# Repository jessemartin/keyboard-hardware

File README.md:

Wireless Keyboard Project: Hardware
===================================

These are [Eagle](https://www.autodesk.com/products/eagle/overview) design files for PCBs used in my wireless keyboard project.

Engineering Overview
--------------------
Each keyboard section runs a [Nordic nRF51822](https://www.nordicsemi.com/eng/Products/Bluetooth-low-energy/nRF51822) in the [Waveshare core51822-b](https://www.waveshare.com/core51822-b.htm) package, powered by a lithium ion battery.

Instead of using a traditional matrix that requires constant scanning (and thereby constant power usage), each key is connected to its own dedicated pin. This way, the chip can enter sleep until interrupted by a key press.

When a key press occurs, it is first debounced to prevent the mechanical switch from generating extra key presses. After that, the pressed keys are collected and transmitted through the [Gazell protocol](https://infocenter.nordicsemi.com/index.jsp?topic=%2Fcom.nordic.infocenter.sdk5.v11.0.0%2Flib_gzp.html&cp=4_0_7_3_10) to the receiver.

The receiver transforms the pressed keys into a matrix and passes that off the the [ATmega32U4 Pro Micro](https://www.sparkfun.com/products/12640), which runs [QMK firmware](https://github.com/qmk/qmk_firmware/). The Pro Micro sends the signal over USB to the computer as input.

Keyboard Layout
---------------
http://www.keyboard-layout-editor.com/#/gists/4d522280e8e3315902466de2c982f663

Folder Structure
----------------
 - `3d` contains [SketchUp](https://app.sketchup.com/app) renderings of what the final product could look like. These are not dimensionally accurate.
 - `fab` contains design rules and CAM settings for [DirtyPCBs](https://dirtypcbs.com/store/pcbs) and [OSH Park](https://oshpark.com/)
 - `lib` contains device libraries that are used by the `receiver` and `keyboard` projects.

PCB Fab Specifications
----------------------
* FR4 fiberglass
* 2 layer
* 1.6mm thickness

Keyboard PCBs
-------------

A single, reversible board is used for each keyboard half. The top of the board is used for the left half, and the bottom for the right half:

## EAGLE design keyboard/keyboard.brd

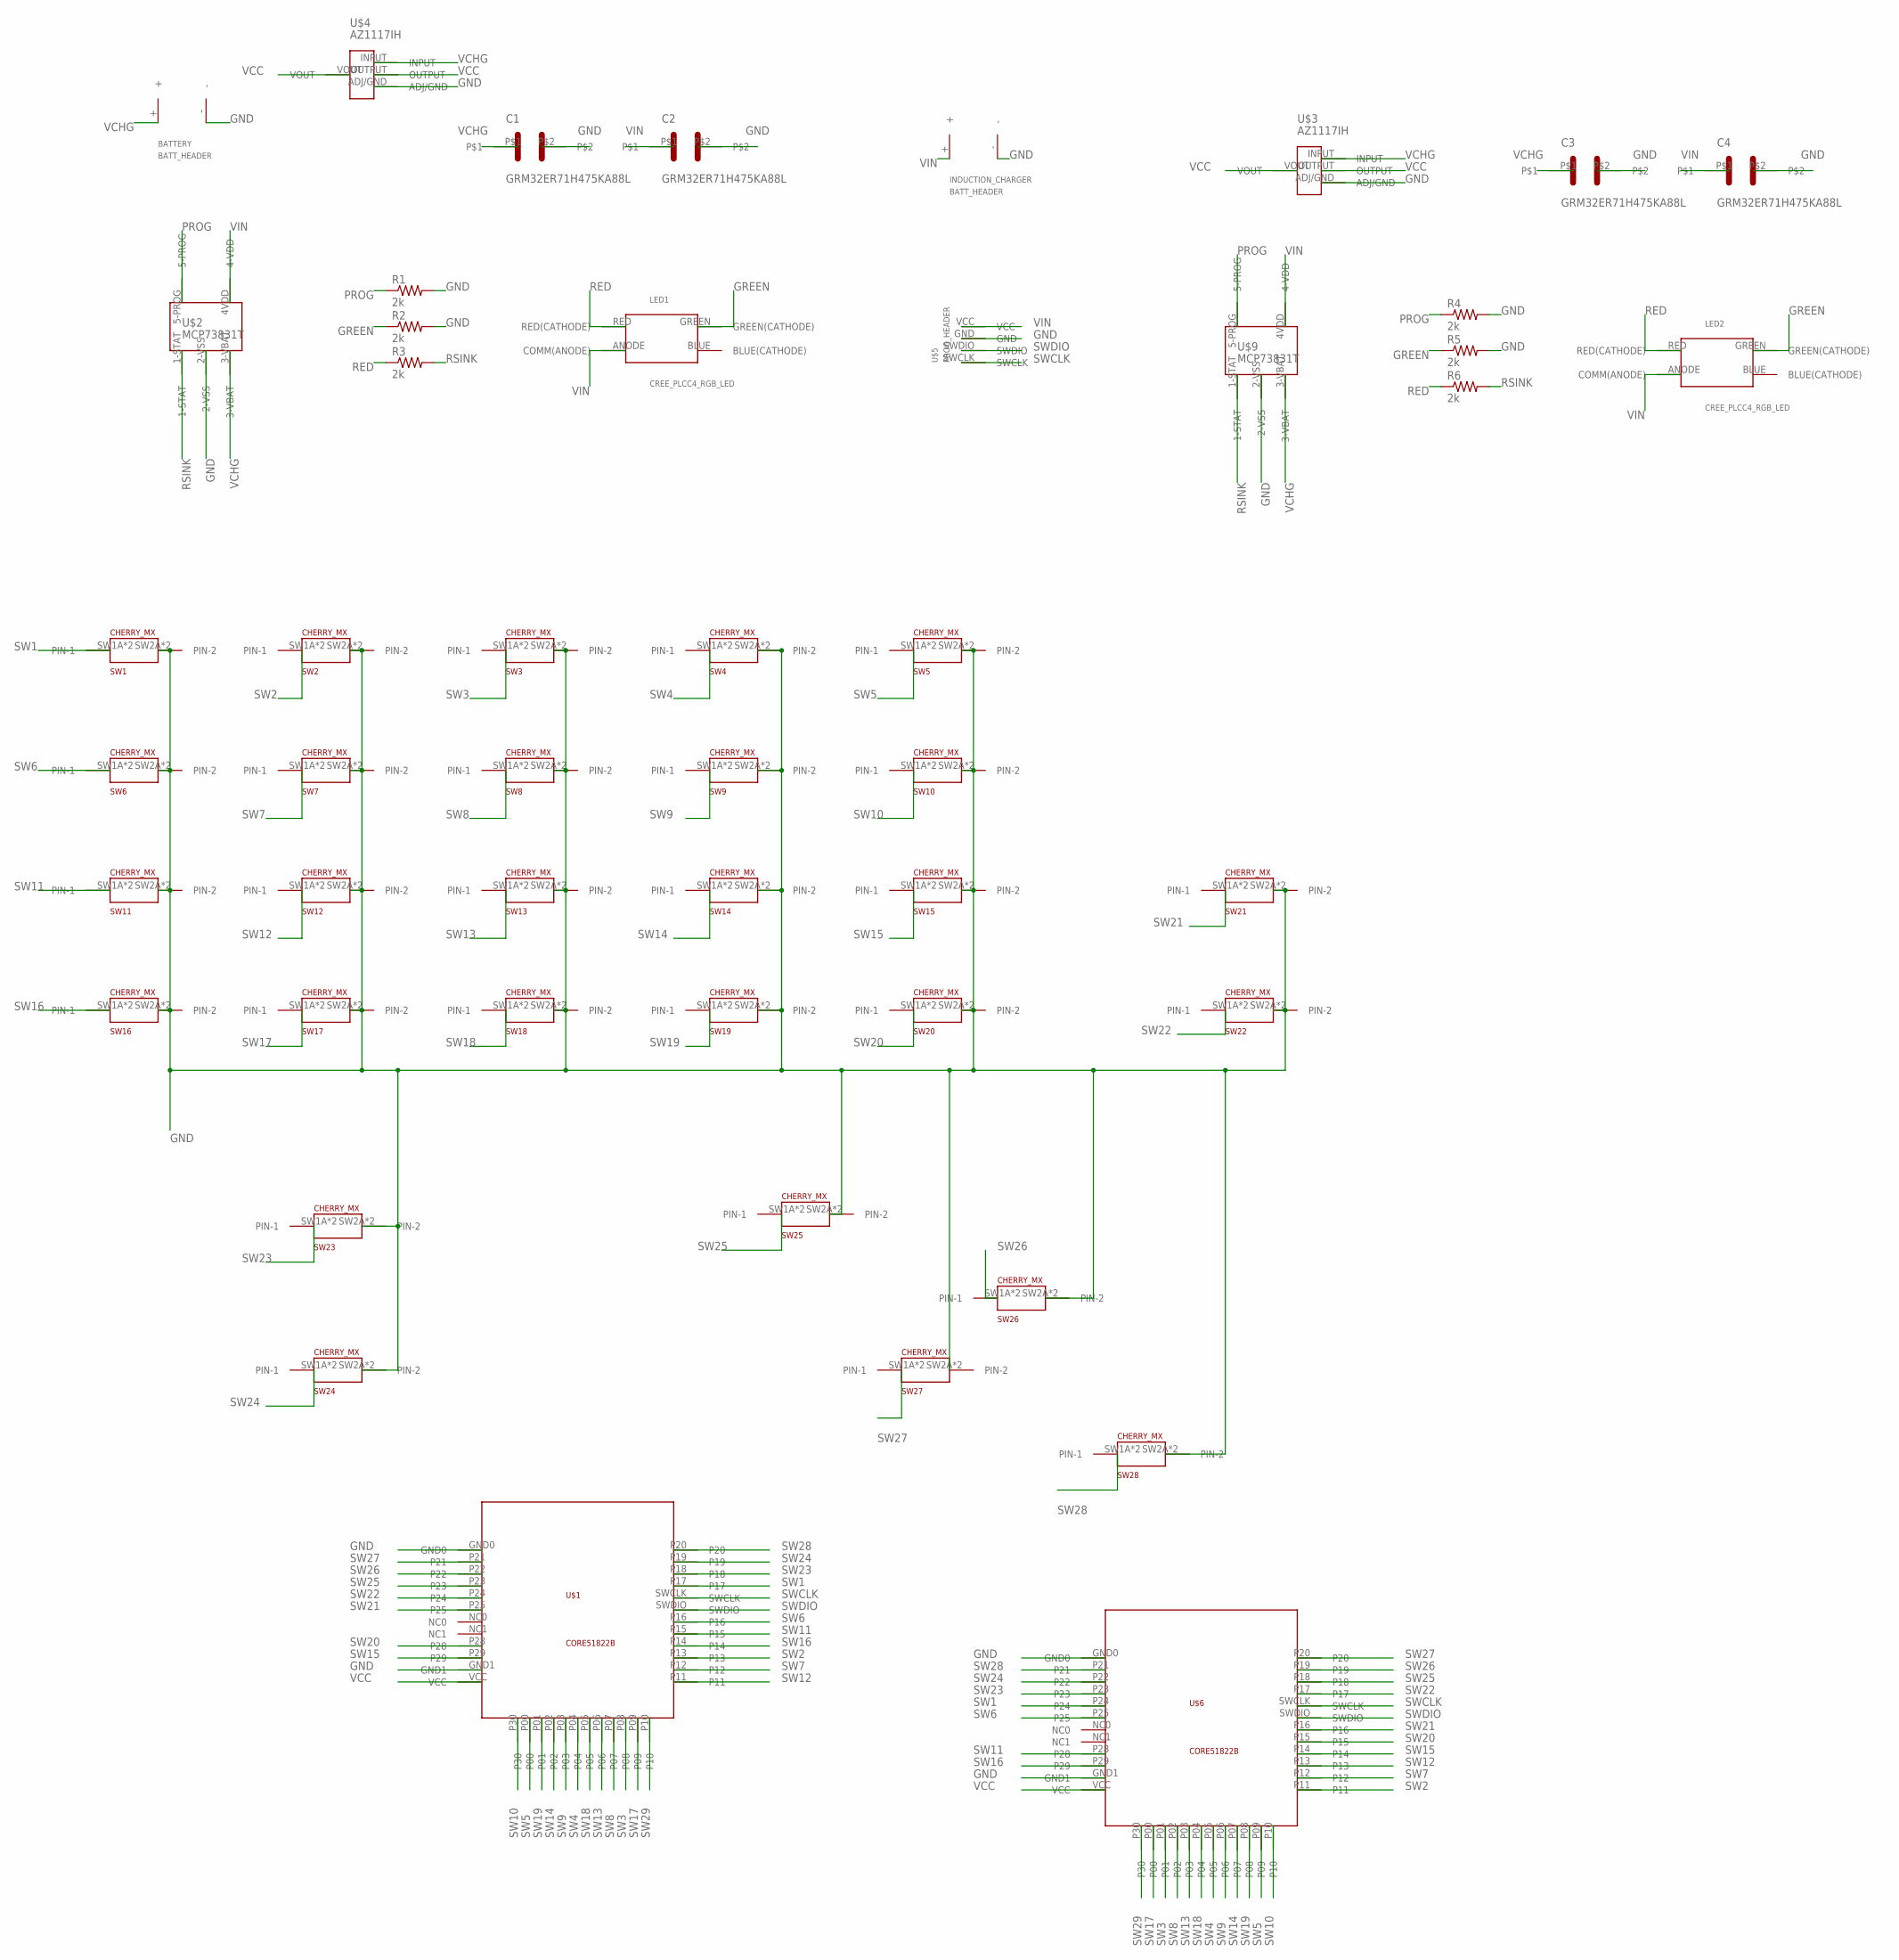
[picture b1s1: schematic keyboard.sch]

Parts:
BATTERY: BATT_HEADER
C1, C2, C3, C4: GRM32ER71H475KA88L
INDUCTION_CHARGER: BATT_HEADER
LED1, LED2: CREE_PLCC4_RGB_LED; 4-PLCC
R1, R2, R3, R4, R5, R6: 2k; R1210
SW1, SW2, SW3, SW4, SW5, SW6, SW7, SW8, SW9, SW10, SW11, SW12, SW13, SW14, SW15, SW16, SW17, SW18, SW19, SW20, SW21, SW22, SW23, SW24, SW25, SW26, SW27, SW28: CHERRY_MX
U$1, U$6: CORE51822B
U$2, U$9: MCP73831T
U$3, U$4: AZ1117IH
U$5: PROG_HEADER

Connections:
GND: BATTERY.-, C1.P$2, C2.P$2, C3.P$2, C4.P$2, INDUCTION_CHARGER.-, R1.2, R2.2, R4.2, R5.2, SW1.SW2A (PIN-2), SW1.SW2B (PIN-2), SW2.SW2A (PIN-2), SW2.SW2B (PIN-2), SW3.SW2A (PIN-2), SW3.SW2B (PIN-2), SW4.SW2A (PIN-2), SW4.SW2B (PIN-2), SW5.SW2A (PIN-2), SW5.SW2B (PIN-2), SW6.SW2A (PIN-2), SW6.SW2B (PIN-2), SW7.SW2A (PIN-2), SW7.SW2B (PIN-2), SW8.SW2A (PIN-2), SW8.SW2B (PIN-2), SW9.SW2A (PIN-2), SW9.SW2B (PIN-2), SW10.SW2A (PIN-2), SW10.SW2B (PIN-2), SW11.SW2A (PIN-2), SW11.SW2B (PIN-2), SW12.SW2A (PIN-2), SW12.SW2B (PIN-2), SW13.SW2A (PIN-2), SW13.SW2B (PIN-2), SW14.SW2A (PIN-2), SW14.SW2B (PIN-2), SW15.SW2A (PIN-2), SW15.SW2B (PIN-2), SW16.SW2A (PIN-2), SW16.SW2B (PIN-2), SW17.SW2A (PIN-2), SW17.SW2B (PIN-2), SW18.SW2A (PIN-2), SW18.SW2B (PIN-2), SW19.SW2A (PIN-2), SW19.SW2B (PIN-2), SW20.SW2A (PIN-2), SW20.SW2B (PIN-2), SW21.SW2A (PIN-2), SW21.SW2B (PIN-2), SW22.SW2A (PIN-2), SW22.SW2B (PIN-2), SW23.SW2A (PIN-2), SW23.SW2B (PIN-2), SW24.SW2A (PIN-2), SW24.SW2B (PIN-2), SW25.SW2A (PIN-2), SW25.SW2B (PIN-2), SW26.SW2A (PIN-2), SW26.SW2B (PIN-2), SW27.SW2A (PIN-2), SW27.SW2B (PIN-2), SW28.SW2A (PIN-2), SW28.SW2B (PIN-2), U$1.GND0, U$1.GND1, U$2.2-VSS, U$3.ADJ/GND, U$4.ADJ/GND, U$5.GND, U$6.GND0, U$6.GND1, U$9.2-VSS
GREEN: LED1.GREEN (GREEN(CATHODE)), LED2.GREEN (GREEN(CATHODE)), R2.1, R5.1
PROG: R1.1, R4.1, U$2.5-PROG, U$9.5-PROG
RED: LED1.RED (RED(CATHODE)), LED2.RED (RED(CATHODE)), R3.1, R6.1
RSINK: R3.2, R6.2, U$2.1-STAT, U$9.1-STAT
SW1: SW1.SW1A (PIN-1), SW1.SW1B (PIN-1), U$1.P17, U$6.P24
SW2: SW2.SW1A (PIN-1), SW2.SW1B (PIN-1), U$1.P13, U$6.P11
SW3: SW3.SW1A (PIN-1), SW3.SW1B (PIN-1), U$1.P08, U$6.P01
SW4: SW4.SW1A (PIN-1), SW4.SW1B (PIN-1), U$1.P04, U$6.P05
SW5: SW5.SW1A (PIN-1), SW5.SW1B (PIN-1), U$1.P00, U$6.P09
SW6: SW6.SW1A (PIN-1), SW6.SW1B (PIN-1), U$1.P16, U$6.P25
SW7: SW7.SW1A (PIN-1), SW7.SW1B (PIN-1), U$1.P12, U$6.P12
SW8: SW8.SW1A (PIN-1), SW8.SW1B (PIN-1), U$1.P07, U$6.P02
SW9: SW9.SW1A (PIN-1), SW9.SW1B (PIN-1), U$1.P03, U$6.P06
SW10: SW10.SW1A (PIN-1), SW10.SW1B (PIN-1), U$1.P30, U$6.P10
SW11: SW11.SW1A (PIN-1), SW11.SW1B (PIN-1), U$1.P15, U$6.P28
SW12: SW12.SW1A (PIN-1), SW12.SW1B (PIN-1), U$1.P11, U$6.P13
SW13: SW13.SW1A (PIN-1), SW13.SW1B (PIN-1), U$1.P06, U$6.P03
SW14: SW14.SW1A (PIN-1), SW14.SW1B (PIN-1), U$1.P02, U$6.P07
SW15: SW15.SW1A (PIN-1), SW15.SW1B (PIN-1), U$1.P29, U$6.P14
SW16: SW16.SW1A (PIN-1), SW16.SW1B (PIN-1), U$1.P14, U$6.P29
SW17: SW17.SW1A (PIN-1), SW17.SW1B (PIN-1), U$1.P09, U$6.P00
SW18: SW18.SW1A (PIN-1), SW18.SW1B (PIN-1), U$1.P05, U$6.P04
SW19: SW19.SW1A (PIN-1), SW19.SW1B (PIN-1), U$1.P01, U$6.P08
SW20: SW20.SW1A (PIN-1), SW20.SW1B (PIN-1), U$1.P28, U$6.P15
SW21: SW21.SW1A (PIN-1), SW21.SW1B (PIN-1), U$1.P25, U$6.P16
SW22: SW22.SW1A (PIN-1), SW22.SW1B (PIN-1), U$1.P24, U$6.P17
SW23: SW23.SW1A (PIN-1), SW23.SW1B (PIN-1), U$1.P18, U$6.P23
SW24: SW24.SW1A (PIN-1), SW24.SW1B (PIN-1), U$1.P19, U$6.P22
SW25: SW25.SW1A (PIN-1), SW25.SW1B (PIN-1), U$1.P23, U$6.P18
SW26: SW26.SW1A (PIN-1), SW26.SW1B (PIN-1), U$1.P22, U$6.P19
SW27: SW27.SW1A (PIN-1), SW27.SW1B (PIN-1), U$1.P21, U$6.P20
SW28: SW28.SW1A (PIN-1), SW28.SW1B (PIN-1), U$1.P20, U$6.P21
SW29: U$1.P10, U$6.P30
SWCLK: U$1.SWCLK, U$5.SWCLK, U$6.SWCLK
SWDIO: U$1.SWDIO, U$5.SWDIO, U$6.SWDIO
VCC: U$1.VCC, U$3.OUTPUT, U$3.VOUT, U$4.OUTPUT, U$4.VOUT, U$6.VCC
VCHG: BATTERY.+, C1.P$1, C3.P$1, U$2.3-VBAT, U$3.INPUT, U$4.INPUT, U$9.3-VBAT
VIN: C2.P$1, C4.P$1, INDUCTION_CHARGER.+, LED1.ANODE (COMM(ANODE)), LED2.ANODE (COMM(ANODE)), U$2.4VDD (4-VDD), U$5.VCC, U$9.4VDD (4-VDD)

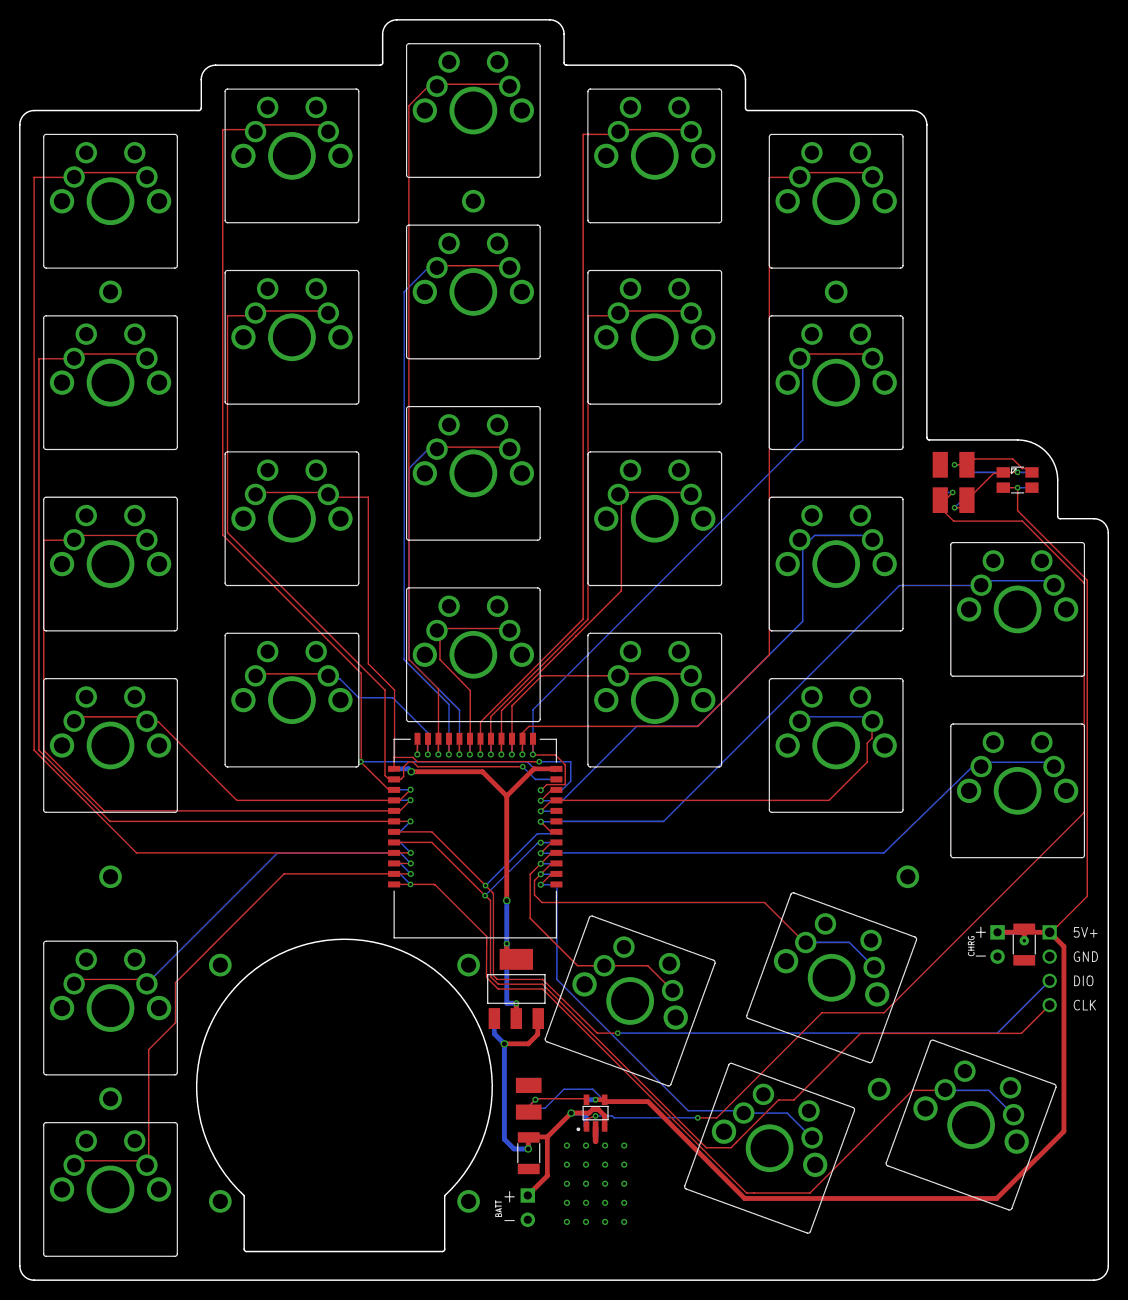
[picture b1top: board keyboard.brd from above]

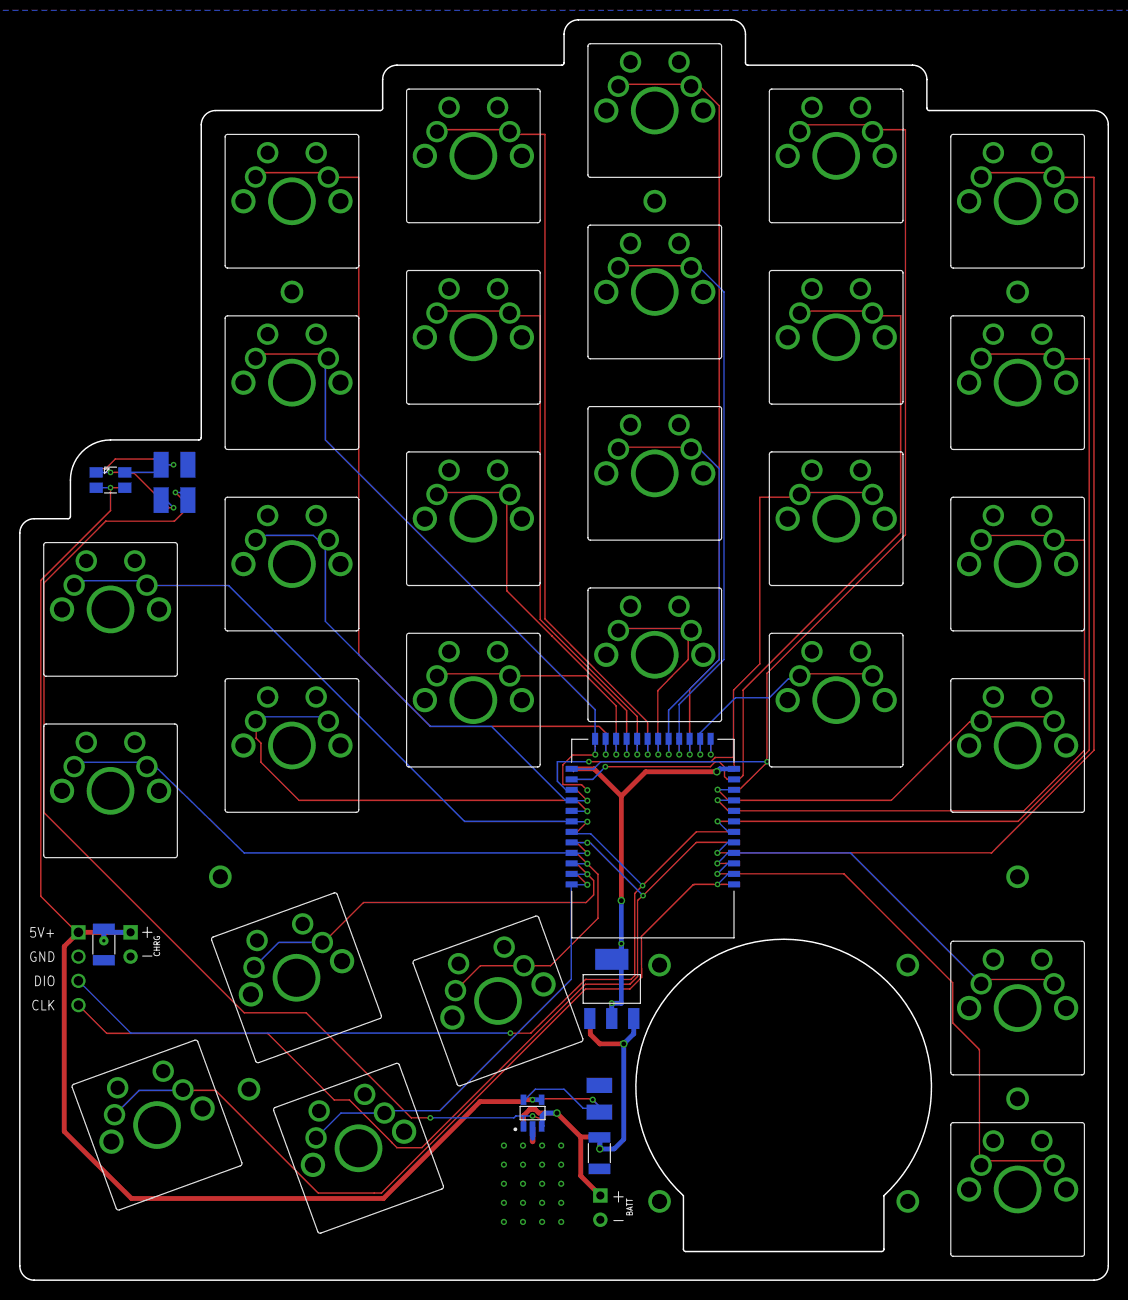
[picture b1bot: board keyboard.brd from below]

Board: 2 copper layers, 114.0 x 132.0 mm, 49 parts (9 on the bottom side), 39 nets.

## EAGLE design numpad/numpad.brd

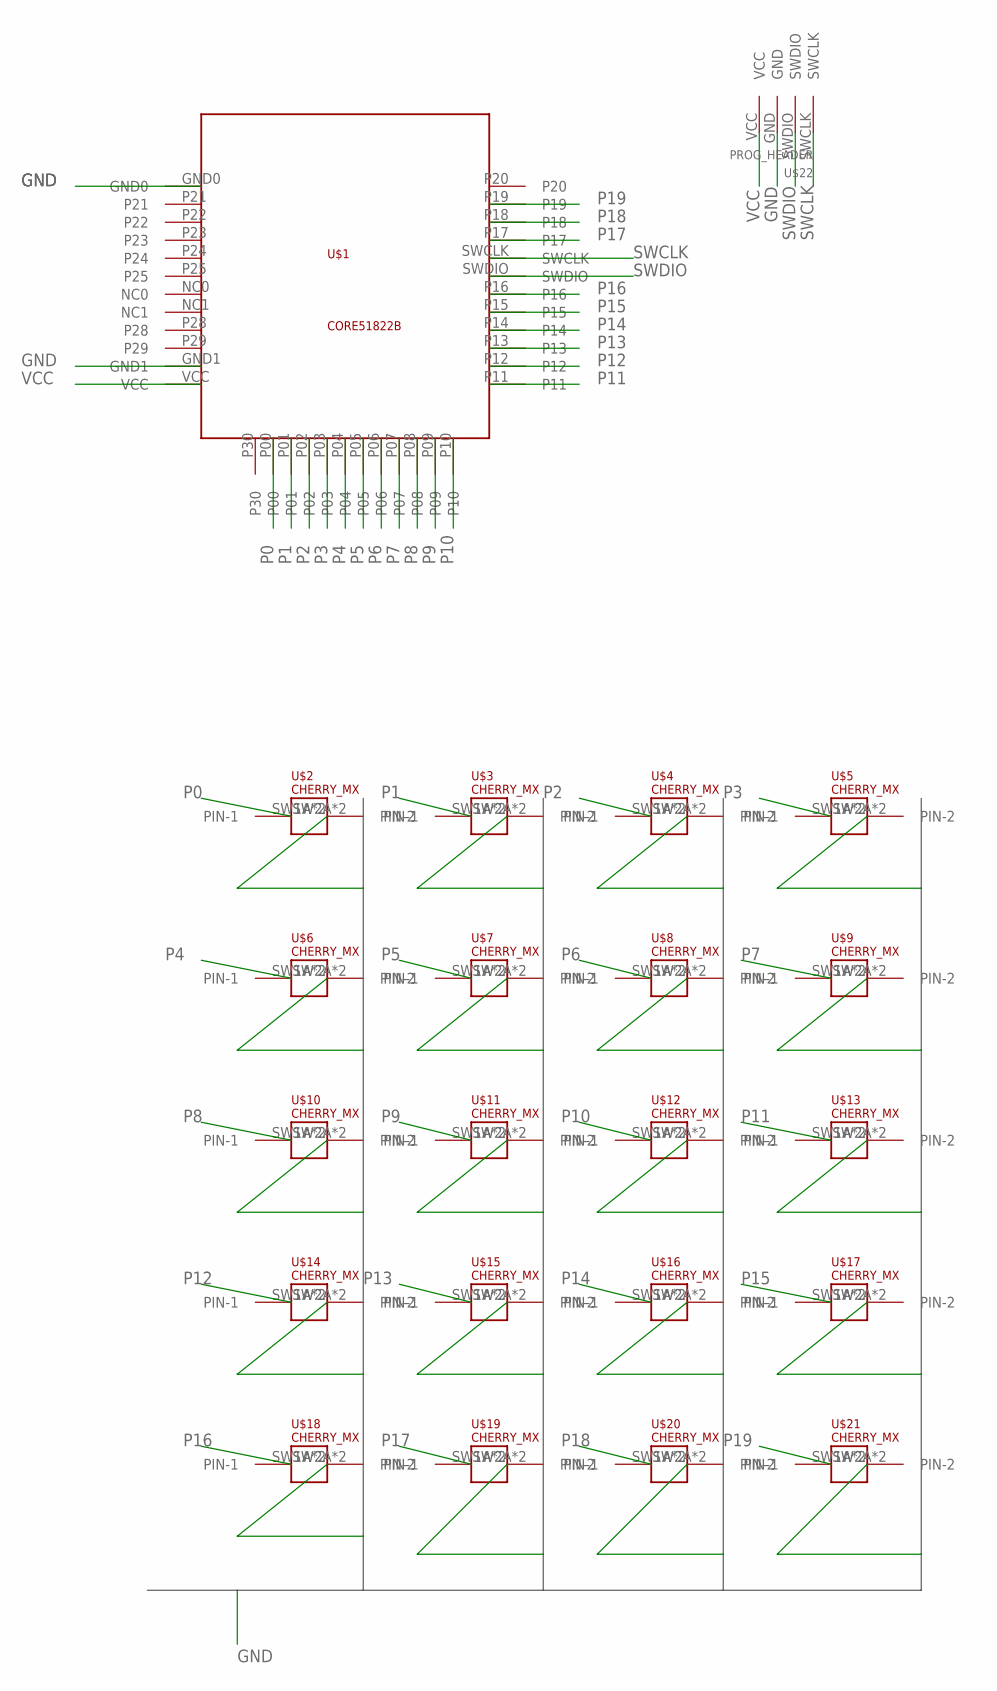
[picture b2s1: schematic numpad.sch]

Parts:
U$1: CORE51822B
U$2, U$3, U$4, U$5, U$6, U$7, U$8, U$9, U$10, U$11, U$12, U$13, U$14, U$15, U$16, U$17, U$18, U$19, U$20, U$21: CHERRY_MX
U$22: PROG_HEADER

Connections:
B$1: U$2.SW2A (PIN-2), U$2.SW2B (PIN-2), U$3.SW2A (PIN-2), U$3.SW2B (PIN-2), U$4.SW2A (PIN-2), U$4.SW2B (PIN-2), U$5.SW2A (PIN-2), U$5.SW2B (PIN-2), U$6.SW2A (PIN-2), U$6.SW2B (PIN-2), U$7.SW2A (PIN-2), U$7.SW2B (PIN-2), U$8.SW2A (PIN-2), U$8.SW2B (PIN-2), U$9.SW2A (PIN-2), U$9.SW2B (PIN-2), U$10.SW2A (PIN-2), U$10.SW2B (PIN-2), U$11.SW2A (PIN-2), U$11.SW2B (PIN-2), U$12.SW2A (PIN-2), U$12.SW2B (PIN-2), U$13.SW2A (PIN-2), U$13.SW2B (PIN-2), U$14.SW2A (PIN-2), U$14.SW2B (PIN-2), U$15.SW2A (PIN-2), U$15.SW2B (PIN-2), U$16.SW2A (PIN-2), U$16.SW2B (PIN-2), U$17.SW2A (PIN-2), U$17.SW2B (PIN-2), U$18.SW2A (PIN-2), U$18.SW2B (PIN-2), U$19.SW2A (PIN-2), U$19.SW2B (PIN-2), U$20.SW2A (PIN-2), U$20.SW2B (PIN-2), U$21.SW2A (PIN-2), U$21.SW2B (PIN-2)
GND: U$1.GND0, U$1.GND1, U$22.GND
P0: U$1.P00, U$2.SW1A (PIN-1), U$2.SW1B (PIN-1)
P1: U$1.P01, U$3.SW1A (PIN-1), U$3.SW1B (PIN-1)
P2: U$1.P02, U$4.SW1A (PIN-1), U$4.SW1B (PIN-1)
P3: U$1.P03, U$5.SW1A (PIN-1), U$5.SW1B (PIN-1)
P4: U$1.P04, U$6.SW1A (PIN-1), U$6.SW1B (PIN-1)
P5: U$1.P05, U$7.SW1A (PIN-1), U$7.SW1B (PIN-1)
P6: U$1.P06, U$8.SW1A (PIN-1), U$8.SW1B (PIN-1)
P7: U$1.P07, U$9.SW1A (PIN-1), U$9.SW1B (PIN-1)
P8: U$1.P08, U$10.SW1A (PIN-1), U$10.SW1B (PIN-1)
P9: U$1.P09, U$11.SW1A (PIN-1), U$11.SW1B (PIN-1)
P10: U$1.P10, U$12.SW1A (PIN-1), U$12.SW1B (PIN-1)
P11: U$1.P11, U$13.SW1A (PIN-1), U$13.SW1B (PIN-1)
P12: U$1.P12, U$14.SW1A (PIN-1), U$14.SW1B (PIN-1)
P13: U$1.P13, U$15.SW1A (PIN-1), U$15.SW1B (PIN-1)
P14: U$1.P14, U$16.SW1A (PIN-1), U$16.SW1B (PIN-1)
P15: U$1.P15, U$17.SW1A (PIN-1), U$17.SW1B (PIN-1)
P16: U$1.P16, U$18.SW1A (PIN-1), U$18.SW1B (PIN-1)
P17: U$1.P17, U$19.SW1A (PIN-1), U$19.SW1B (PIN-1)
P18: U$1.P18, U$20.SW1A (PIN-1), U$20.SW1B (PIN-1)
P19: U$1.P19, U$21.SW1A (PIN-1), U$21.SW1B (PIN-1)
SWCLK: U$1.SWCLK, U$22.SWCLK
SWDIO: U$1.SWDIO, U$22.SWDIO
VCC: U$1.VCC, U$22.VCC

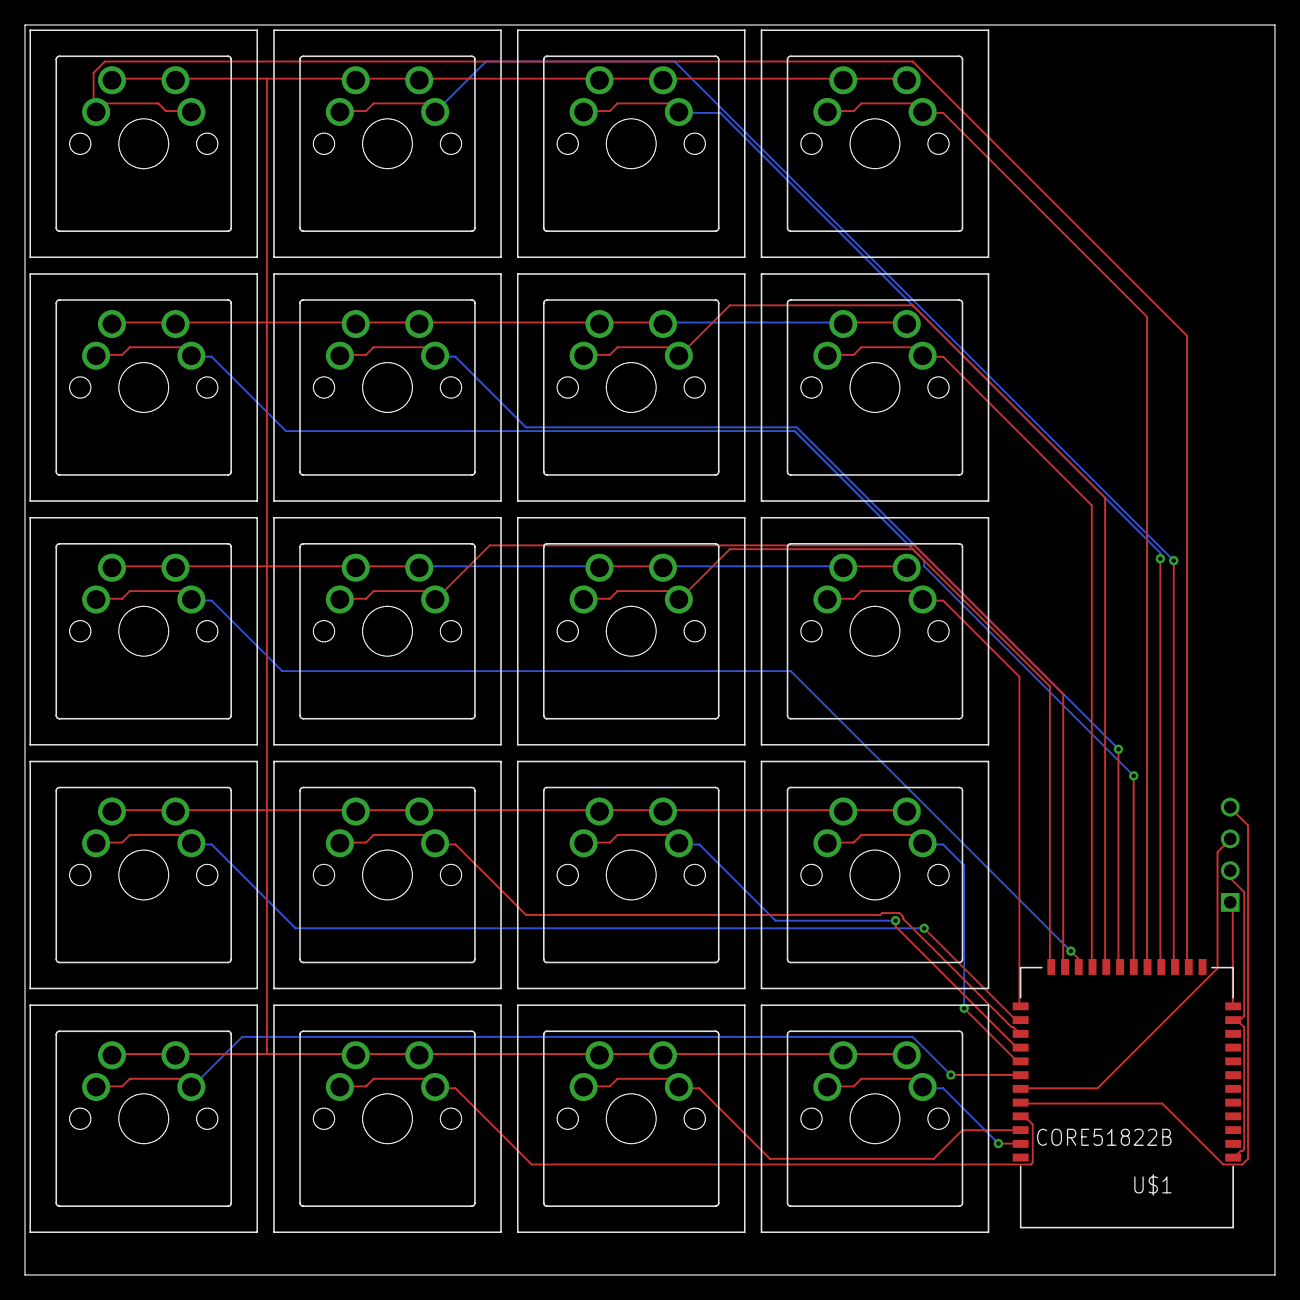
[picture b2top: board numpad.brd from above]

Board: 2 copper layers, 100.0 x 100.0 mm, 22 parts (0 on the bottom side), 25 nets.

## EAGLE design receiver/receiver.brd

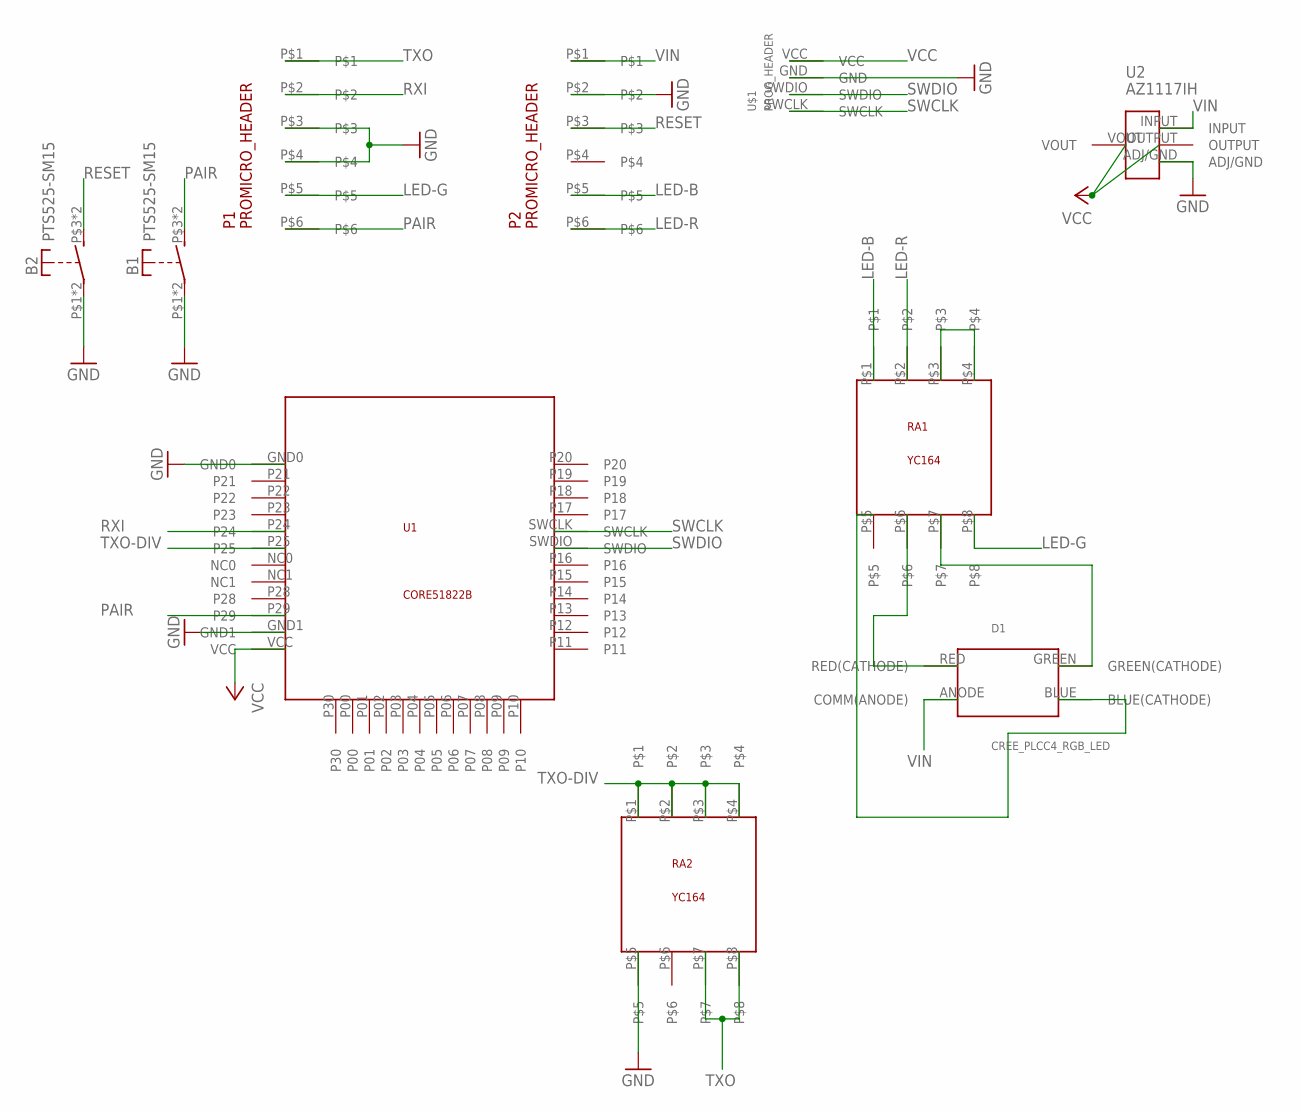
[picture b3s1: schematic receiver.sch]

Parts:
B1, B2: PTS525-SM15
D1: CREE_PLCC4_RGB_LED; 4-PLCC
P1, P2: PROMICRO_HEADER
RA1, RA2: YC164
U1: CORE51822B
U2: AZ1117IH
U$1: PROG_HEADER

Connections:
GND: B1.P$1, B1.P$2, B2.P$1, B2.P$2, P1.P$3, P1.P$4, P2.P$2, RA2.P$5, U1.GND0, U1.GND1, U2.ADJ/GND, U$1.GND
LED-B: P2.P$5, RA1.P$1
LED-G: P1.P$5, RA1.P$8
LED-R: P2.P$6, RA1.P$2
unnamed: RA1.P$3, RA1.P$4
unnamed: D1.GREEN (GREEN(CATHODE)), RA1.P$7
unnamed: D1.RED (RED(CATHODE)), RA1.P$6
unnamed: D1.BLUE (BLUE(CATHODE)), RA1.P$5
PAIR: B1.P$3 (S), B1.P$4 (S), P1.P$6, U1.P29
RESET: B2.P$3 (S), B2.P$4 (S), P2.P$3
RXI: P1.P$2, U1.P24
SWCLK: U1.SWCLK, U$1.SWCLK
SWDIO: U1.SWDIO, U$1.SWDIO
TXO: P1.P$1, RA2.P$7, RA2.P$8
TXO-DIV: RA2.P$1, RA2.P$2, RA2.P$3, RA2.P$4, U1.P25
VCC: U1.VCC, U2.OUTPUT, U2.VOUT, U$1.VCC
VIN: D1.ANODE (COMM(ANODE)), P2.P$1, U2.INPUT

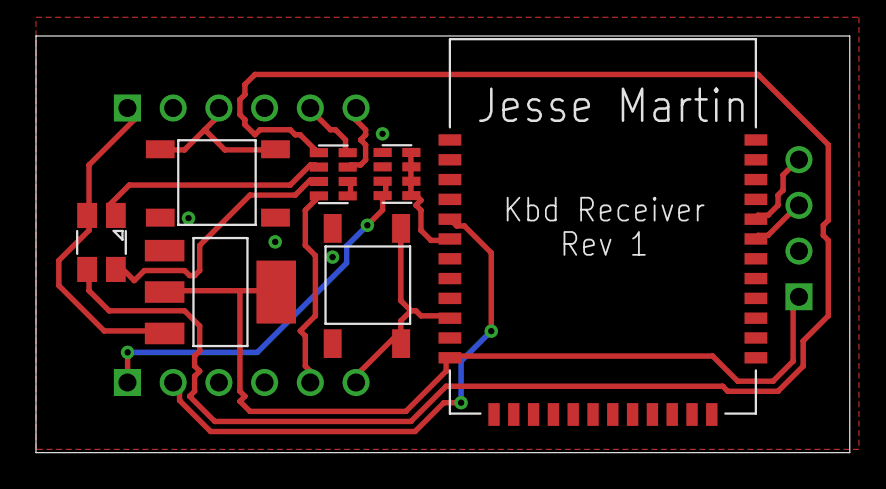
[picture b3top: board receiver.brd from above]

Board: 2 copper layers, 45.2 x 23.1 mm, 10 parts (0 on the bottom side), 17 nets.

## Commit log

2017-11-08 add core51822b
2017-11-09 add schematic and board
2017-11-09 add receiver
2017-11-09 add core51822 lib
2017-11-09 finish core51822b device
2017-11-09 restructure
2017-11-09 add gitignore
2017-11-09 remove ignored files
2017-11-09 add readme
2017-11-09 remove irrelevant image
2017-11-09 add pro micro pinout image
2017-11-09 remove unfinished files
2017-11-09 add lib readme
2017-11-09 add names to core51822b
2017-11-11 add yc164 resistor array
2017-11-11 add yc164 resistor to receiver
2017-11-11 add az1117l images
2017-11-12 layout components
2017-11-12 add pts525-sm15 spst push button switch
2017-11-12 fix typo in readme
2017-11-13 update core51822b tplace
2017-11-13 update cree tplace
2017-11-13 update pts tplace
2017-11-13 update yc164 tplace
2017-11-14 remove dimensions to enable routing
2017-11-14 update board
2017-11-14 re-route
2017-11-14 add za1117ih and remove old pro micro
2017-11-14 add programming header
2017-11-14 include programming header on board
2017-11-14 add switch tplace
2017-11-14 add fab specs to readme
2017-11-14 add 2nd layer ground and vias
2017-11-15 finish routing vias
2017-11-15 update led pin names
2017-11-15 update drill size to 10mil
2017-11-15 reposition prog header
2017-11-16 generate gerbers
2017-11-16 revise board layout
2017-11-16 generate v2 gerbers
2017-11-16 update silkscreen
2017-11-16 include gerber zip
2017-11-16 add fab drc and cam settings
2017-11-16 generate dirtypcb gerbers
2017-11-16 include archive
2017-11-17 add keyboard layout to readme
2017-11-18 cleanup gerbers
2017-11-28 add layout image
2017-12-05 update image
2017-12-05 add cherry_mx lib
2017-12-05 add numpad
2017-12-05 add cherry mx dimensions
2017-12-05 add keyboard
2017-12-06 add labels to cherry mx package
2017-12-06 update numpad
2017-12-06 initial key layout
2017-12-06 move header inward to allow for 90° bend
2017-12-07 wire up switches
2017-12-07 widen cherry mx symbol
2017-12-07 run autorouter
2017-12-07 rearrange pins to eliminate vias
2017-12-07 consistently align keys
2017-12-07 add TODO
2017-12-07 add MCP73831T LiPo CMC
2017-12-08 use pads for cherry mx mounting pins
2017-12-08 update mcp73831t pinout
2017-12-08 connect mcp73831t charging circuit
2017-12-10 update resistors
2017-12-10 add GRM32ER71H475KA88L capacitor
2017-12-10 mirror charging circuit on board bottom
2017-12-10 smash labels and values
2017-12-10 reroute
2017-12-10 add induction charger header
2017-12-11 update layout
2017-12-11 finish routing
2017-12-11 miter board corners
2017-12-11 consolidate nrf51 nets
2017-12-11 cleanup vias
2017-12-11 update names
2017-12-11 add more heatsink vias
2017-12-12 create plate cutout file
2017-12-12 move nrf51 to accommodate battery
2017-12-12 cleanup names and values
2017-12-12 remove numpad
2017-12-13 start minimizing footprint
2017-12-13 standardize signal thickness
2017-12-13 resize board
2017-12-13 update board edge profile
2017-12-13 update heatsink pad on mcp73831t
2017-12-13 generate test gerbers
2017-12-14 expose mcp73831t heatsink pad copper
2017-12-14 add rough, inaccurate 3d models
2017-12-16 add header labels to board bottom
2017-12-16 move battery hole to dimension layer
2017-12-17 remove airwire
2017-12-17 update layout image
2017-12-17 update routing for oshpark
2017-12-17 add board images
2017-12-17 add images to readme:
2017-12-17 update gerbers
2017-12-17 cleanup trace and text
2017-12-17 update cherrymx bPlace
2017-12-17 fix prog header stops
2017-12-17 regenerate gerbers
2017-12-17 update board images
2017-12-18 increase mcp73831t heatsink pad size
2017-12-18 increase corner radii to 1.5mm
2017-12-19 remove todo
2017-12-19 increase drill size
2017-12-19 increase vcc via size
2017-12-19 update stops
2017-12-19 update pads
2017-12-19 redesign heatsink
2017-12-19 add mounting holes
2017-12-20 extend battery bay
2017-12-20 add laser cut outline
2017-12-20 adjust battery
2017-12-20 update routing
2017-12-20 full size plate
2018-01-22 add voltage regulator
2018-03-21 add gw12rhp switch
